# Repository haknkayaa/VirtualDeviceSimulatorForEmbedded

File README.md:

# Virtual Device Simulator for Embedded (VDS4E)

**Run Embedded Linux applications against virtual SPI, I²C, GPIO, UART and Ethernet devices without the physical target board.**

VDS4E is a hardwareless integration-testing environment for Embedded Linux software. It exposes virtual peripherals through normal Linux userspace interfaces such as `/dev/spidevX.Y`, `/dev/i2c-N`, `/dev/gpiochipN` and PTYs, allowing native x86_64 builds of production applications and standard Linux tools to exercise stateful device models on a development workstation.

VDS4E is not a CPU or board emulator. It focuses on the boundary between an Embedded Linux application and the device interfaces it already uses.

## See VDS4E

[Website](https://vds4e.dev) · [Watch the product film](https://vds4e.dev/#product-film) · [GitHub Releases](https://github.com/haknkayaa/VirtualDeviceSimulatorForEmbedded/releases)

VDS4E includes a browser-based engineering workbench for live device bring-up,
adapter configuration, register inspection, transaction tracing, logic analysis,
scenario execution and fault diagnosis. The UI runs with the packaged server;
no separate Web server is required for release installations.

## Why VDS4E?

Traditional mocks often replace application code paths. Full-system emulators model much more of the machine than many application-level tests need. VDS4E sits between those approaches:

- **No VDS-specific API in the application.** Production code continues to use the Linux device ABI.
- **Kernel-visible interfaces.** SPI, I²C and GPIO can be exercised through normal device nodes; UART uses a standard PTY.
- **Stateful peripherals.** Device packages can model registers, bitfields, memory, state machines, timed operations, faults and reset behavior.
- **Declarative models.** Peripheral behavior lives in versioned device packages rather than application-side test doubles.
- **Cross-device topology.** Public device signals can drive GPIO lines, enabling flows such as sensor DRDY → GPIO edge → bus read.
- **Observable execution.** Transactions, registers, state, faults, scenarios and telemetry are available through the control plane.
- **Automation friendly.** Headless scenarios can produce JSON and JUnit results for integration and CI workflows.

## Architecture

```text
┌──────────────────────────────────────────────────────────────────────┐
│ Embedded Linux application / standard Linux tool                    │
│ spidev_test · i2c-tools · libgpiod tools · normal application code  │
└───────────────────────────────┬──────────────────────────────────────┘
                                │ normal Linux userspace ABI
                                ▼
┌──────────────────────────────────────────────────────────────────────┐
│ VDS4E host adapters                                                  │
│ SPI CUSE · I²C CUSE · gpio-sim · UART PTY                           │
└───────────────────────────────┬──────────────────────────────────────┘
                                │ framed Protobuf / Unix socket
                                ▼
┌──────────────────────────────────────────────────────────────────────┐
│ VDS4E runtime                                                        │
│ device registry · registers · behavior · virtual time · topology     │
└───────────────────────────────┬──────────────────────────────────────┘
                                │
                                ▼
┌──────────────────────────────────────────────────────────────────────┐
│ Declarative device packages                                         │
│ model · flows · scenarios · fixtures · docs · assets                 │
└──────────────────────────────────────────────────────────────────────┘

Control & observability: REST API · WebSocket events · React Web UI
```

The detailed design and architectural boundaries are documented in [VDS4E_ARCHITECTURE.md](VDS4E_ARCHITECTURE.md).

## Supported interfaces

| Interface | Linux-facing endpoint | Runtime support | Typical clients |
| --- | --- | --- | --- |
| SPI / spidev | `/dev/spidevX.Y` via CUSE | `generic-spi-command` | production spidev applications, upstream `spidev_test` |
| I²C / i2c-dev | `/dev/i2c-N` via CUSE | `generic-i2c-register`, AT24C EEPROM | `i2cdetect`, `i2cget`, `i2cset`, `i2ctransfer`, libi2c applications |
| GPIO | real `/dev/gpiochipN` via kernel `gpio-sim` | `generic-gpio-bank` | `gpiodetect`, `gpioinfo`, `gpioget`, `gpioset`, `gpiomon`, libgpiod applications |
| UART / TTY | kernel-assigned `/dev/pts/N` | `generic-uart-responder` | applications using `open/read/write` and termios |
| QSPI multi-lane / DTR | native VDS4E transaction path | SPI wire-setting validation | VDS4E native clients |
| Ethernet / CAN / USB | — | not implemented | — |

SPI and I²C CUSE adapters and the GPIO `gpio-sim` integration require appropriate host-kernel support and privileges. UART PTY operation is unprivileged.

## What's available on `main`

| Capability | What you can do |
| --- | --- |
| **Bring-up-first Overview** | Follow the Linux device node → adapter → virtual peripheral path, inspect live traffic, runtime state, problem diagnostics, scenario progress and bus activity. |
| **Register and device workbench** | Inspect registers, bitfields, state, commands, fault controls, configuration and transaction history for each device. |
| **Transaction and logic analysis** | Examine bus requests/responses, protocol data, failures, virtual signals and capture timelines; filter failed transactions and deep-link to a capture. |
| **Declarative device modeling** | Build versioned SPI, I²C, GPIO and UART device packages with registers, command behavior, state transitions, time-dependent operations and fault injection. |
| **Board-level signal topology** | Route a modeled sensor's DRDY/IRQ output to a kernel-visible GPIO line; inspect connections, current signal levels and pending delayed deliveries in the UI or `GET /api/v1/topology`. |
| **Device Tree import** | Draft SPI/I²C/GPIO packages from a DTS file, plus a reviewed board summary and a GPIO-interrupt `topology.yaml` draft where supported. |
| **Scenario coverage** | See which declared commands, registers, states, transitions and faults a run actually exercised. Export machine-readable JSON and JUnit properties. |
| **Real Linux application examples** | Run sample C applications against SPI flash, I²C EEPROM, GPIO (libgpiod) and UART (PTY), using ordinary Linux interfaces rather than VDS4E-specific mocks. |

These are source-tree capabilities, not a promise that every feature above is
included in the latest published `.deb`. See [the changelog](CHANGELOG.md)
for changes made after the latest tagged release. DTS import produces editable
drafts, **not** validated device-specific behavior extracted automatically
from a hardware description.

## Quick start

### Install a release package

Tagged releases publish an `amd64` Debian package and SHA-256 checksum.
The latest published package is **v0.1.2**; newer capabilities described above
may require a build from the current `main` branch.

Download the package from [GitHub Releases](https://github.com/haknkayaa/VirtualDeviceSimulatorForEmbedded/releases), then install it:

```shell
sudo apt install ./vds4e_0.1.2_amd64.deb
```

Validate the installed configuration:

```shell
vds4e --check-config
```

Start VDS4E:

```shell
vds4e
```

Then open `http://127.0.0.1:8080/`. The same process serves the Web UI,
REST API, WebSocket event stream, and Unix-socket transaction data plane.

To run it as a system service instead:

```shell
sudo systemctl enable --now vds4e
```

The package installs the unit but does not enable or start it automatically.

The package installs:

- `vds4e`, `vds-server` and `vds-cli`
- SPI, I²C, GPIO and UART host adapters
- the built Web UI assets
- schemas and bundled example device models
- example Embedded Linux tools
- `/etc/vds4e/vds-server.yaml`

Package installation intentionally does not load privileged kernel modules automatically.

### Run from source

Building or running from source requires Rust (`rustup` / `cargo`), Node.js/npm, and system build tools. See [Getting started: Prerequisites](docs/guides/getting-started.md#prerequisites) for one-step installation instructions.

For development:

```shell
git clone https://github.com/haknkayaa/VirtualDeviceSimulatorForEmbedded.git
cd VirtualDeviceSimulatorForEmbedded
./run.sh
```

The development launcher starts the Web UI, control API and transaction data plane. See [Getting started](docs/guides/getting-started.md) for privilege details.

For the staged production-style build:

```shell
./configure
./build.sh
sudo ./install
```

## Device packages

A device is a self-contained, versionable package:

```text
my-device/
├── device-package.yaml
├── model/
│   └── device.yaml
├── flows/
│   └── behavior.yaml
├── scenarios/
├── fixtures/
├── docs/
└── assets/
```

Create and validate a package:

```shell
vds-cli device-package new ./my-sensor \
  --id my-sensor \
  --name "My Sensor" \
  --bus i2c

vds-cli device-package validate ./my-sensor
```

The bundled examples include generic SPI/I²C/GPIO/UART devices, an Ethernet ARP/ICMP host, AT24C EEPROM models and a Micron MT25QL256 flash model.

### Example applications

The repository includes standalone Embedded Linux examples that exercise the
same interfaces as ordinary production applications:

| Example | Linux interface | What it exercises |
| --- | --- | --- |
| [Micron MT25QL256](examples/micron-mt25ql256-embedded/) | SPI `/dev/spidevX.Y` | flash identification and command transactions |
| [Atmel AT24C256](examples/atmel-at24c256-embedded/) | I²C `/dev/i2c-N` | EEPROM address and data transactions |
| [Generic GPIO tool](examples/generic-gpio-embedded/) | libgpiod `/dev/gpiochipN` | line inspection, input/output and edge monitoring |
| [UART ping](examples/generic-uart-embedded/) | PTY `/dev/pts/N` | serial request/response |
| [Ethernet TAP](docs/guides/ethernet.md) | TAP `vdsN` | ARP resolution and IPv4 ICMP Echo from normal Linux tools |

From a source checkout with prerequisites installed:

```shell
./examples/run_all.sh --build-only
```

Start VDS4E and load the relevant adapters and device bindings before running
the examples. `./examples/run_all.sh` also attempts to exercise discovered
device nodes; it may need host privileges for the kernel-backed interfaces.
The actual `gpiochipN` and PTY numbers depend on the host.

See the [Device Package SDK](docs/development/device-package-sdk.md), [behavior-flow reference](docs/device-models/device-behavior-flow-reference.md), and package/model schemas under [schemas/](schemas/).

## Cross-device signals

Device models can expose public boolean output signals and connect them to device-driven GPIO lines through a board topology.

A typical flow is:

```text
sensor schedules conversion completion
        ↓
sensor.drdy becomes high
        ↓
VDS4E topology routes the signal
        ↓
virtual GPIO line changes
        ↓
/dev/gpiochipN reports an edge
        ↓
application reads the sensor over SPI/I²C
        ↓
read-clear status deasserts DRDY
```

This allows application behavior based on interrupts/data-ready lines to be exercised without adding simulator-specific code to the application.

The workbench and `GET /api/v1/topology` also expose a **read-only view** of
the attached connections, last sampled source levels and delayed deliveries.

See [Topology](docs/guides/topology.md).

## Scenarios and deterministic device behavior

Headless scenarios use a manual virtual clock. Device-model operations such as state transitions, delayed actions, faults and timed write/erase behavior can therefore be reproduced independently of host CPU speed.

Example:

```shell
vds-cli scenario run \
  device-models/examples/micron-mt25ql256aba8esf-0sit/scenarios/01-read-jedec-id.yaml \
  --config config/vds-server.yaml \
  --json-output /tmp/result.json \
  --junit-output /tmp/result.xml
```

The live server uses a real-time-backed simulator clock. Live runs therefore retain deterministic device-model semantics but are still subject to normal operating-system scheduling jitter. VDS4E does not claim whole-system or bit-for-bit determinism for live native processes.

## Scenario coverage

Scenario results can report model-level coverage, so a passing test does not
silently imply that every declared behavior was exercised. Coverage tracks:

- commands sent to a modeled device;
- registers reached through normal device operations;
- entered/exited states and observed state transitions;
- triggered fault definitions.

You can inspect coverage in the CLI output, scenario JSON results, JUnit
properties, the Visual Scenario Editor and the Overview's latest-run panel.
Coverage is **informational**; it does not automatically fail CI when a
threshold is missed.

Read the [coverage reference](docs/development/scenario-coverage.md)
and [ADR 0013](docs/adr/0013-measure-scenario-coverage-against-device-models.md)
for the exact counting rules and current SPI-scenario scope.

## Control and observability

The server provides:

- REST control API
- WebSocket event stream with bounded replay
- optional SQLite event persistence
- transaction and register inspection
- device state and fault control
- scenario execution
- adapter management
- React Web UI

High-frequency hardware transactions do **not** travel over REST. Native adapters use the framed Protobuf Unix-socket data plane.

Default development endpoints:

```text
Control API:  http://127.0.0.1:8080/api/v1
Web UI:       http://127.0.0.1:4174
Data plane:   /tmp/vds4e.sock
```

## Hardware-description import

The `vds-importer` crate can draft declarative models from:

- CMSIS-SVD register descriptions
- Device Tree source

Importer output is intentionally a starting point rather than a finished behavioral model. Device-specific semantics still need to be reviewed and completed by the model author.

Draft device packages for enabled SPI, I²C and GPIO peripherals in a board's Device Tree (available on `main`):

```shell
vds-cli import dts board.dts --output drafts/
```

When a peripheral's `interrupt-parent` is a GPIO controller of the board, the
import also drafts that controller as a GPIO bank and writes
`drafts/topology.yaml`, connecting the peripheral's new `irq` output (driven by
bit 0 of a placeholder `IRQ_STATE` register) to the line its `interrupts`
names. Every draft, and the topology, is loaded the way the server loads them
before the command succeeds. `drafts/board.md` lists each package with its bus controller,
endpoint (SPI chip select or I2C address), compatible strings and interrupts,
the nodes that were skipped (disabled, or a bus without a VDS4E runtime), and
the `device_packages` entries to add to `vds-server.yaml`. Pass
`--include-disabled` to draft `status = "disabled"` nodes too.

## What VDS4E does not simulate

VDS4E provides functional peripheral simulation. It does not currently model:

- CPU instruction execution
- a complete SoC or board boot
- electrical characteristics or signal integrity
- controller DMA/IRQ timing
- analog behavior
- Ethernet, CAN or USB runtime devices
- full-system checkpoint/restore or record/replay

Use QEMU, Renode or another full-system platform when CPU/SoC emulation is the requirement. Use hardware-in-the-loop and real-target testing for electrical, timing and hardware-integration validation.

For recorded, unprivileged device replay, [umockdev](https://github.com/martinpitt/umockdev) may be a lighter fit. VDS4E is aimed at cases where stateful modeled behavior, kernel-visible interfaces, shared device state and cross-device interaction matter.

## Verification

The regular CI validates the Rust workspace, Web UI, native adapters and example applications.

Equivalent local checks include:

```shell
cargo fmt --all -- --check
cargo clippy --workspace --all-targets --locked -- -D warnings
cargo test --workspace --locked

npm --prefix apps/vds-web ci
npm --prefix apps/vds-web run lint
npm --prefix apps/vds-web run typecheck
npm --prefix apps/vds-web run test:run
npm --prefix apps/vds-web run build
```

A real Linux ABI E2E harness is available under `tests/e2e/` for privileged integration testing with standard Linux tools and kernel-backed interfaces.

## Documentation

| Document | Purpose |
| --- | --- |
| [Documentation index](docs/README.md) | map of user, contributor and architecture documentation |
| [Getting started](docs/guides/getting-started.md) | prerequisites, development workspace, staged build and installation |
| [First virtual device](docs/tutorials/first-virtual-device.md) | create an I²C model and exercise it through a real `/dev/i2c-N` endpoint |
| [Control-plane API](docs/guides/api.md) | REST resources, error contract and replayable WebSocket events |
| [Architecture](VDS4E_ARCHITECTURE.md) | authoritative system architecture and boundaries |
| [Testing](docs/guides/testing.md) | local checks, native adapters, real Linux ABI E2E and CI scope |
| [Releases](docs/guides/releases.md) | version/tag rules and Debian release workflow |
| [Troubleshooting](docs/guides/troubleshooting.md) | common CUSE, gpio-sim, permissions, PTY and configuration issues |
| [SPI / I²C / GPIO / UART](docs/guides/) | Linux host-interface guides and examples |
| [Ethernet TAP](docs/guides/ethernet.md) | Linux TAP adapter, ARP/ICMP host model and configuration |
| [Topology guide](docs/guides/topology.md) | cross-device signal routing |
| [Device Package SDK](docs/development/device-package-sdk.md) | package contract and author workflow |
| [Scenario coverage](docs/development/scenario-coverage.md) | coverage accounting for commands, registers, states, transitions and faults |
| [C example applications](examples/) | hardware-facing sample tools and run-all script |
| [ADRs](docs/adr/README.md) | architecture decisions |
| [Roadmap](docs/ROADMAP.md) | planned capabilities |
| [Contributing](CONTRIBUTING.md) | development and contribution guidance |
| [Security](SECURITY.md) | security policy |

## Project boundaries

The project intentionally keeps these responsibilities separate:

- the server owns authoritative virtual-device state;
- host adapters translate Linux ABIs and do not contain device semantics;
- the Web UI is a control and observability client, not a device runtime;
- high-frequency transactions use the native Unix-socket data plane;
- behavior comes from declarative device packages;
- privileged kernel integration is isolated from the core runtime.

These boundaries are part of the product design, not just implementation details.

## License

Licensed under the [Apache License 2.0](LICENSE).

## Maintainer

Hakan Kaya ([@haknkayaa](https://github.com/haknkayaa))

VDS4E is currently developed independently by Hakan Kaya. The open-source core is available under Apache 2.0.

Contact: [hakan@vds4e.dev](mailto:hakan@vds4e.dev) · [Project website](https://vds4e.dev)

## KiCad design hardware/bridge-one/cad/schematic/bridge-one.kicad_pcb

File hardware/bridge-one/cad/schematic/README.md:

# Bridge One schematic (generated)

`design.py` is the single source of truth: functional groups, parts, pin-to-net
maps and the notes printed in each group box. Do not edit the `.kicad_sch`
files by hand; regenerate them.

```bash
python3 symbols/make_symbols.py      # project symbols (RSV translators, TPS2553)
python3 ../footprints/make_footprints.py   # TI DQA / YXC land patterns
python3 render.py                    # root + one hierarchical sheet per group
python3 board.py                     # bridge-one.kicad_pcb: all parts, pad nets, linked to symbols
kicad-cli sch erc bridge-one.kicad_sch
kicad-cli sch export netlist --format kicadsexpr -o /tmp/bridge-one.net bridge-one.kicad_sch
python3 tools/verify_netlist.py /tmp/bridge-one.net   # must report 0 mismatches
kicad-cli sch export pdf -o bridge-one-schematic.pdf bridge-one.kicad_sch
```

Nets used in more than one group become global labels; group-internal nets are
local labels. Every symbol pin must be assigned a net or listed as no-connect,
or `render.py` refuses to write the schematic.

`board.py` places every design.py part (anchors from ../preview/generate_preview.py
plus NEW_ANCHORS; passives auto-placed next to the part they connect to), assigns
pad nets, links footprints to schematic symbols (deterministic UUIDs), restores
the JLCPCB 4-layer rules in bridge-one.kicad_pro, and writes the STEP and
placement.json used by ../enclosure/generate_enclosure.py.

Status (sch0.4, 2026-10-14): TPS3808G01 FPGA rail supervisor and VTREF overvoltage
disconnect added (research/vtref-ovp-and-fpga-supervisor.md); PCA9306 replaced by
PCA9617ADP (research/i2c-translator-replacement.md); review fixes applied (research/review-codex-sch0.1.md,
research/review-kicad-happy-sch0.1.md, research/footprint-verification.md).
ERC: only intentional warnings (unused translator inputs tied to GND, TPS22917 QOD
tied to VOUT). Netlist matches design.py exactly. PCB: 215 footprints, unrouted;
DRC errors are only unrouted nets, H2/H4 inside the module's conservative antenna
keepout (symmetric holes by request) and a GCT USB-C library footprint hole note.

Open: power budget vs F1 hold with aux outputs enabled, ESP32 open-drain low <= 0.4 V
for the PCA9617A B side (bench), OLED FPC pin-1 mapping check on samples, 32 MB PSRAM
option, KLS USB-C footprint swap, routing and bottom silkscreen cleanup.

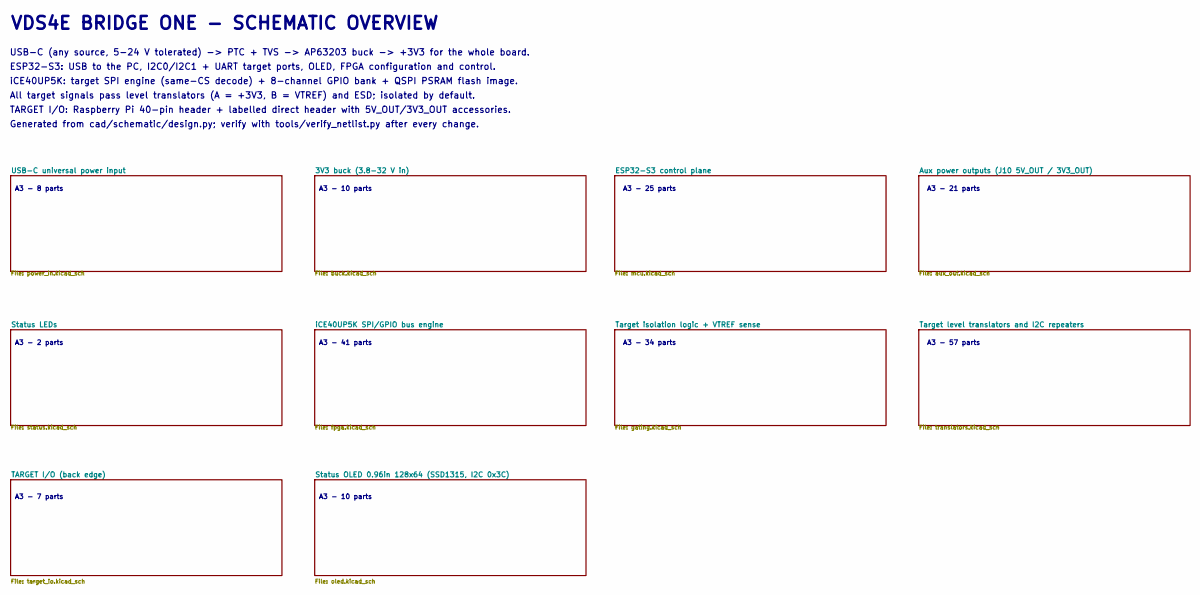
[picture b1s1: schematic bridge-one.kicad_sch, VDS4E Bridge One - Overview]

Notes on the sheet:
USB-C (any source, 5-24 V tolerated) -> PTC + TVS -> AP63203 buck -> +3V3 for the whole board.
iCE40UP5K: target SPI engine (same-CS decode) + 8-channel GPIO bank + QSPI PSRAM flash image.
VDS4E BRIDGE ONE - SCHEMATIC OVERVIEW
A3 - 10 parts
A3 - 8 parts
A3 - 7 parts
TARGET I/O: Raspberry Pi 40-pin header + labelled direct header with 5V_OUT/3V3_OUT accessories.
A3 - 21 parts
All target signals pass level translators (A = +3V3, B = VTREF) and ESD; isolated by default.
A3 - 2 parts
A3 - 25 parts
Generated from cad/schematic/design.py; verify with tools/verify_netlist.py after every change.
A3 - 41 parts
A3 - 57 parts
A3 - 34 parts
ESP32-S3: USB to the PC, I2C0/I2C1 + UART target ports, OLED, FPGA configuration and control.

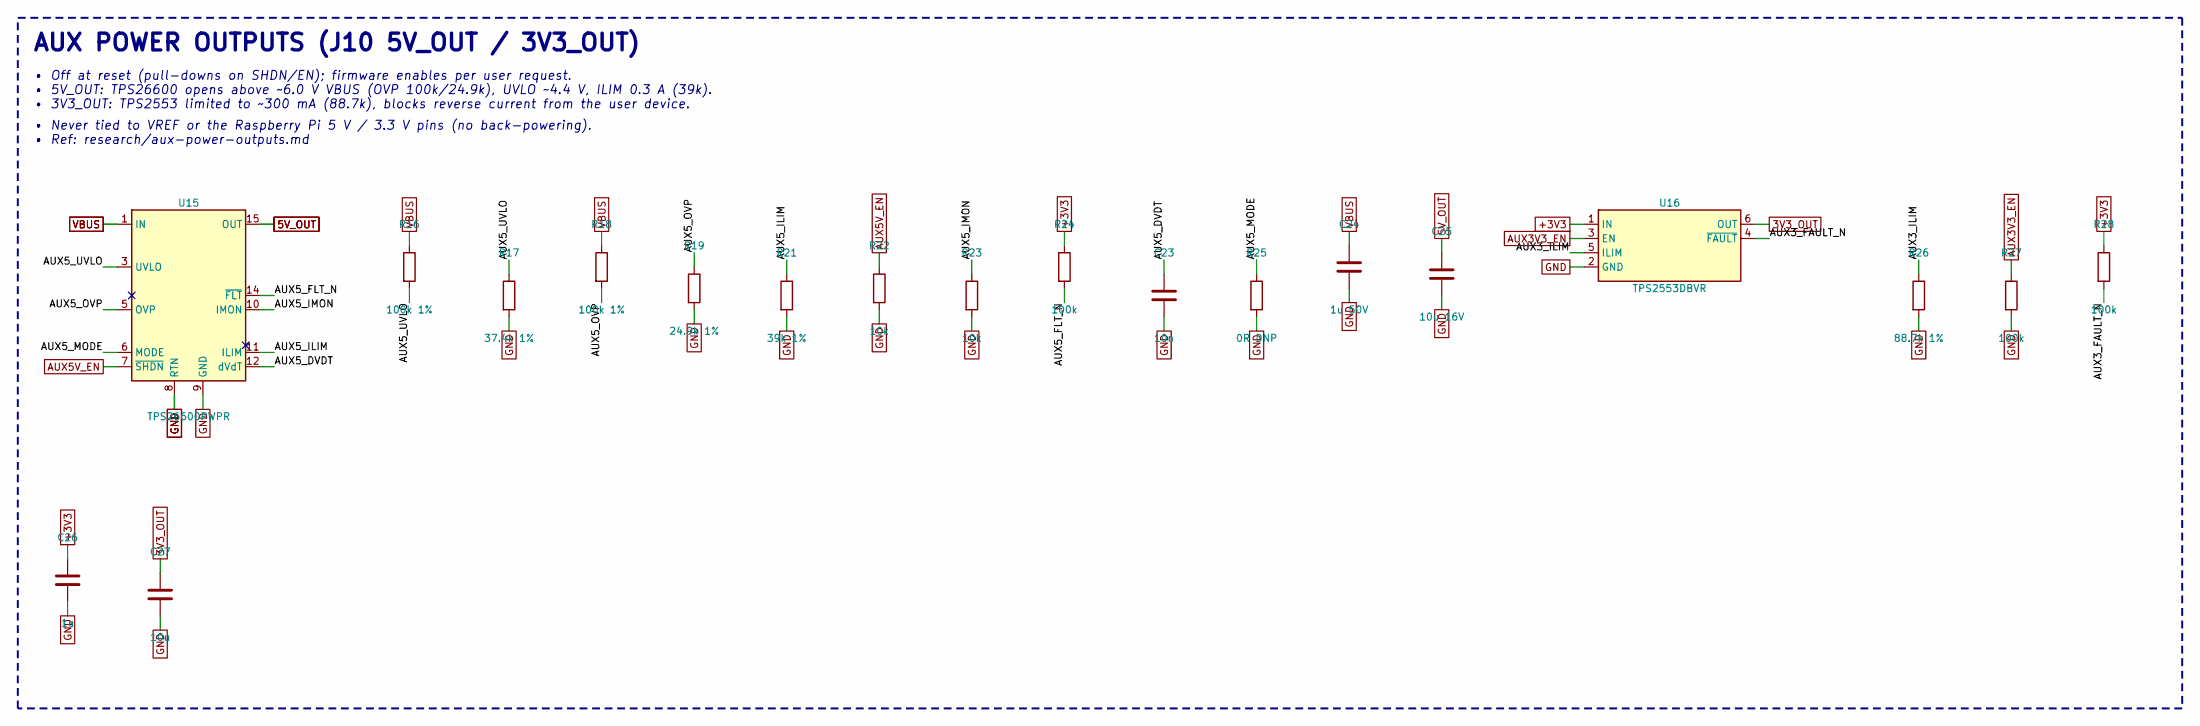
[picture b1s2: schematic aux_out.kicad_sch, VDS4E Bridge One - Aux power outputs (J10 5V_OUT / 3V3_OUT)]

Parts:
C23: 10n; C_0402_1005Metric
C24: 1u 50V; C_0603_1608Metric
C25: 10u 16V; C_0805_2012Metric
C26: 1u; C_0402_1005Metric
C27: 10u; C_0805_2012Metric
R16, R18: 100k 1%; R_0402_1005Metric
R17: 37.4k 1%; R_0402_1005Metric
R19: 24.9k 1%; R_0402_1005Metric
R21: 39k 1%; R_0402_1005Metric
R22, R23: 10k; R_0402_1005Metric
R24, R27, R28: 100k; R_0402_1005Metric
R25: 0R DNP; R_0402_1005Metric
R26: 88.7k 1%; R_0402_1005Metric
U15: TPS26600PWPR; HTSSOP-16-1EP_4.4x5mm_P0.65mm_EP3.4x5mm; MPN TPS26600PWPR
U16: TPS2553DBVR; SOT-23-6; MPN TPS2553DBVR

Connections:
3V3_OUT: C27.1, U16.6 (OUT); also elsewhere on the board
5V_OUT: C25.1, U15.15 (OUT), U15.16 (OUT); also elsewhere on the board
AUX3V3_EN: R27.1, U16.3 (EN); also elsewhere on the board
AUX3_FAULT_N: R28.2, U16.4 (~FAULT)
AUX3_ILIM: R26.1, U16.5 (ILIM)
AUX5V_EN: R22.1, U15.7 (~SHDN); also elsewhere on the board
AUX5_DVDT: C23.1, U15.12 (dVdT)
AUX5_FLT_N: R24.2, U15.14 (~FLT)
AUX5_ILIM: R21.1, U15.11 (ILIM)
AUX5_IMON: R23.1, U15.10 (IMON)
AUX5_MODE: R25.1, U15.6 (MODE)
AUX5_OVP: R18.2, R19.1, U15.5 (OVP); also elsewhere on the board
AUX5_UVLO: R16.2, R17.1, U15.3 (UVLO); also elsewhere on the board
VBUS: C24.1, R16.1, R18.1, U15.1 (IN), U15.2 (IN); also elsewhere on the board

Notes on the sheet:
• Never tied to VREF or the Raspberry Pi 5 V / 3.3 V pins (no back-powering).
• 5V_OUT: TPS26600 opens above ~6.0 V VBUS (OVP 100k/24.9k), UVLO ~4.4 V, ILIM 0.3 A (39k).
• 3V3_OUT: TPS2553 limited to ~300 mA (88.7k), blocks reverse current from the user device.
AUX POWER OUTPUTS (J10 5V_OUT / 3V3_OUT)
• Ref: research/aux-power-outputs.md
• Off at reset (pull-downs on SHDN/EN); firmware enables per user request.

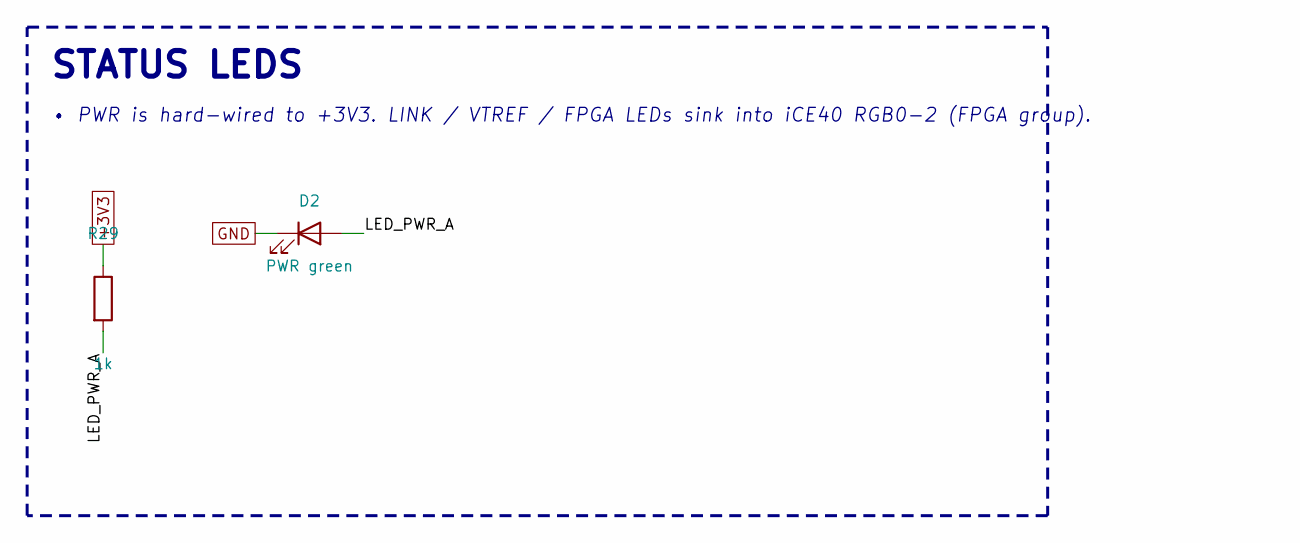
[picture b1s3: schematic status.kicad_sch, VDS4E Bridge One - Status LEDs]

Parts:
D2: PWR green; LED_0603_1608Metric
R29: 1k; R_0402_1005Metric

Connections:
LED_PWR_A: D2.2 (A), R29.2

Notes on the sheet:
• PWR is hard-wired to +3V3. LINK / VTREF / FPGA LEDs sink into iCE40 RGB0-2 (FPGA group).
STATUS LEDS

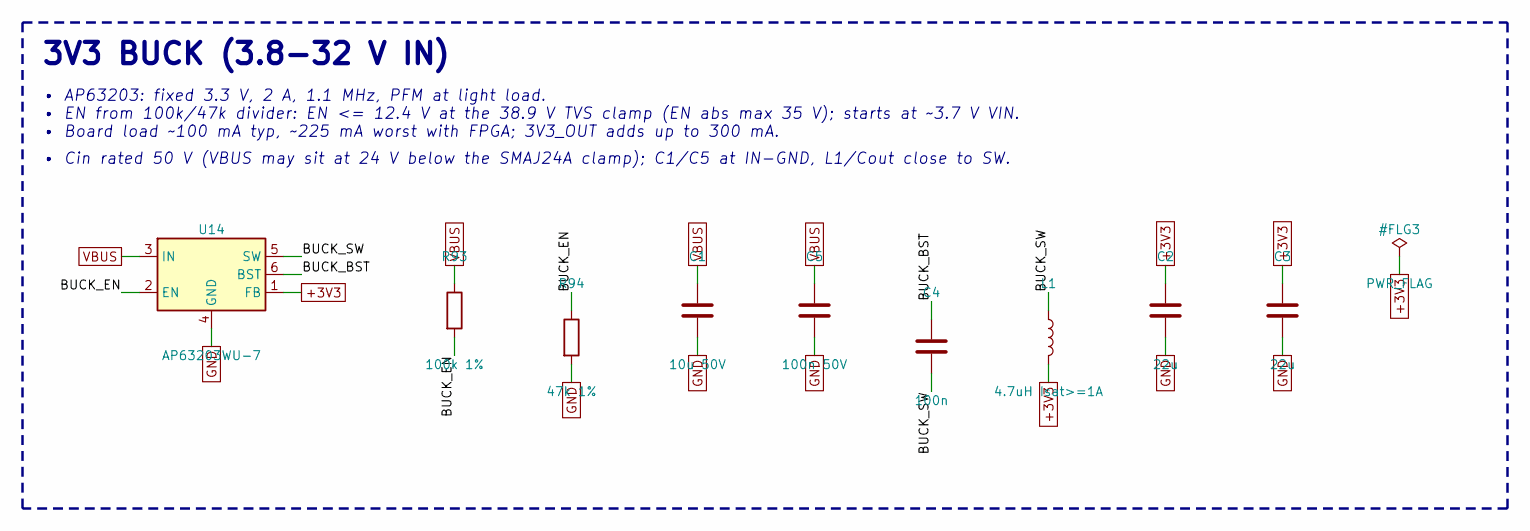
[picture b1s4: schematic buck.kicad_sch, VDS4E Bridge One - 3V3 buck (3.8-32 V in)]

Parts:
C1: 10u 50V; C_1206_3216Metric
C2, C3: 22u; C_0805_2012Metric
C4: 100n; C_0603_1608Metric
C5: 100n 50V; C_0603_1608Metric
L1: 4.7uH Isat>=1A; L_Taiyo-Yuden_NR-30xx; MPN NR3015N4R7A
R93: 100k 1%; R_0402_1005Metric
R94: 47k 1%; R_0402_1005Metric
U14: AP63203WU-7; TSOT-23-6; MPN AP63203WU-7

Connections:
BUCK_BST: C4.1, U14.6 (BST)
BUCK_EN: R93.2, R94.1, U14.2 (EN)
BUCK_SW: C4.2, L1.1, U14.5 (SW)
VBUS: C1.1, C5.1, R93.1, U14.3 (IN); also elsewhere on the board

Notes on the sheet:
• AP63203: fixed 3.3 V, 2 A, 1.1 MHz, PFM at light load.
• Cin rated 50 V (VBUS may sit at 24 V below the SMAJ24A clamp); C1/C5 at IN-GND, L1/Cout close to SW.
3V3 BUCK (3.8-32 V IN)
• EN from 100k/47k divider: EN <= 12.4 V at the 38.9 V TVS clamp (EN abs max 35 V); starts at ~3.7 V VIN.
• Board load ~100 mA typ, ~225 mA worst with FPGA; 3V3_OUT adds up to 300 mA.

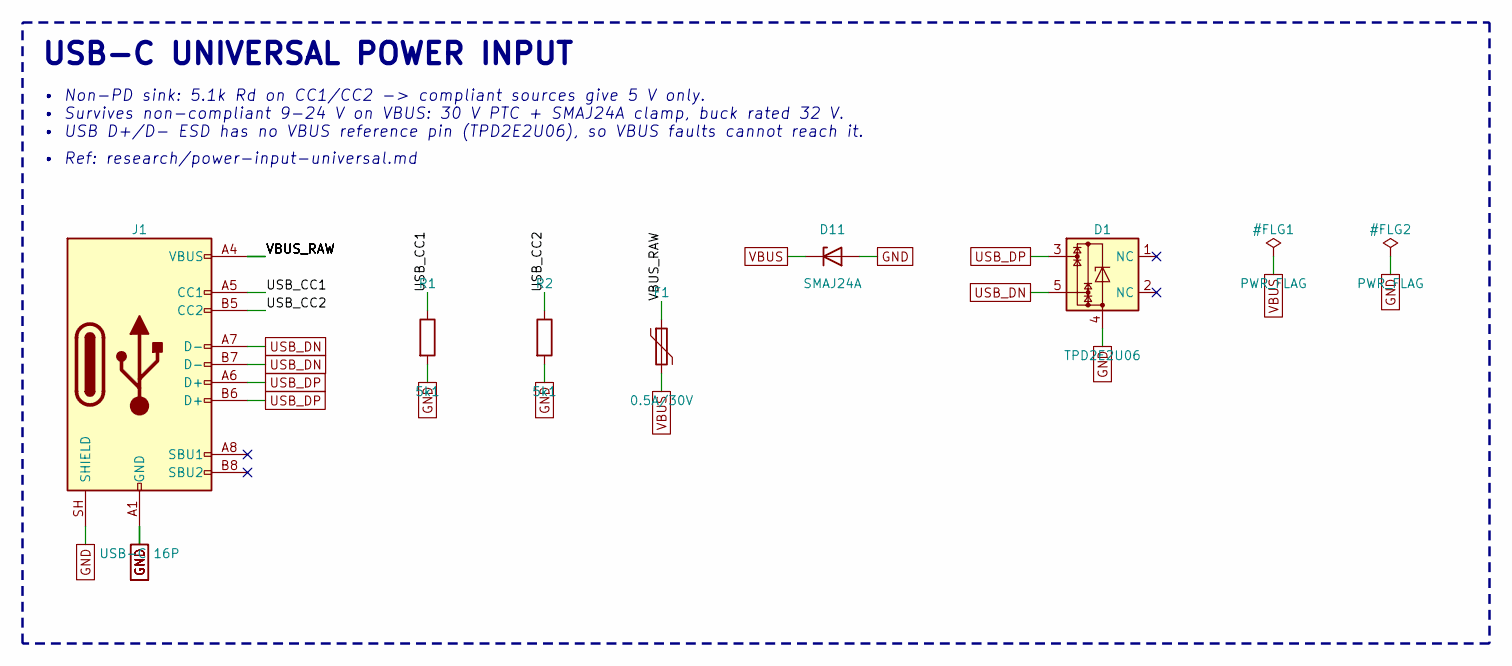
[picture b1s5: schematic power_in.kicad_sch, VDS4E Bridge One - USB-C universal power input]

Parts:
D1: TPD2E2U06; SOT-553; MPN TPD2E2U06DRLR
D11: SMAJ24A; D_SMA; MPN SMAJ24A
F1: 0.5A/30V; Fuse_1812_4532Metric; MPN BSMD1812-050-30V
J1: USB-C 16P; USB_C_Receptacle_GCT_USB4105-xx-A_16P_TopMnt_Horizontal; MPN USB4105-GF-A-120
R1, R2: 5k1; R_0402_1005Metric

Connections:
USB_CC1: J1.A5 (CC1), R1.1
USB_CC2: J1.B5 (CC2), R2.1
USB_DN: D1.5, J1.A7 (D-), J1.B7 (D-); also elsewhere on the board
USB_DP: D1.3, J1.A6 (D+), J1.B6 (D+); also elsewhere on the board
VBUS: D11.1 (K), F1.2; also elsewhere on the board
VBUS_RAW: F1.1, J1.A4 (VBUS), J1.A9 (VBUS), J1.B4 (VBUS), J1.B9 (VBUS)

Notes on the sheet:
• Ref: research/power-input-universal.md
• USB D+/D- ESD has no VBUS reference pin (TPD2E2U06), so VBUS faults cannot reach it.
• Survives non-compliant 9-24 V on VBUS: 30 V PTC + SMAJ24A clamp, buck rated 32 V.
• Non-PD sink: 5.1k Rd on CC1/CC2 -> compliant sources give 5 V only.
USB-C UNIVERSAL POWER INPUT

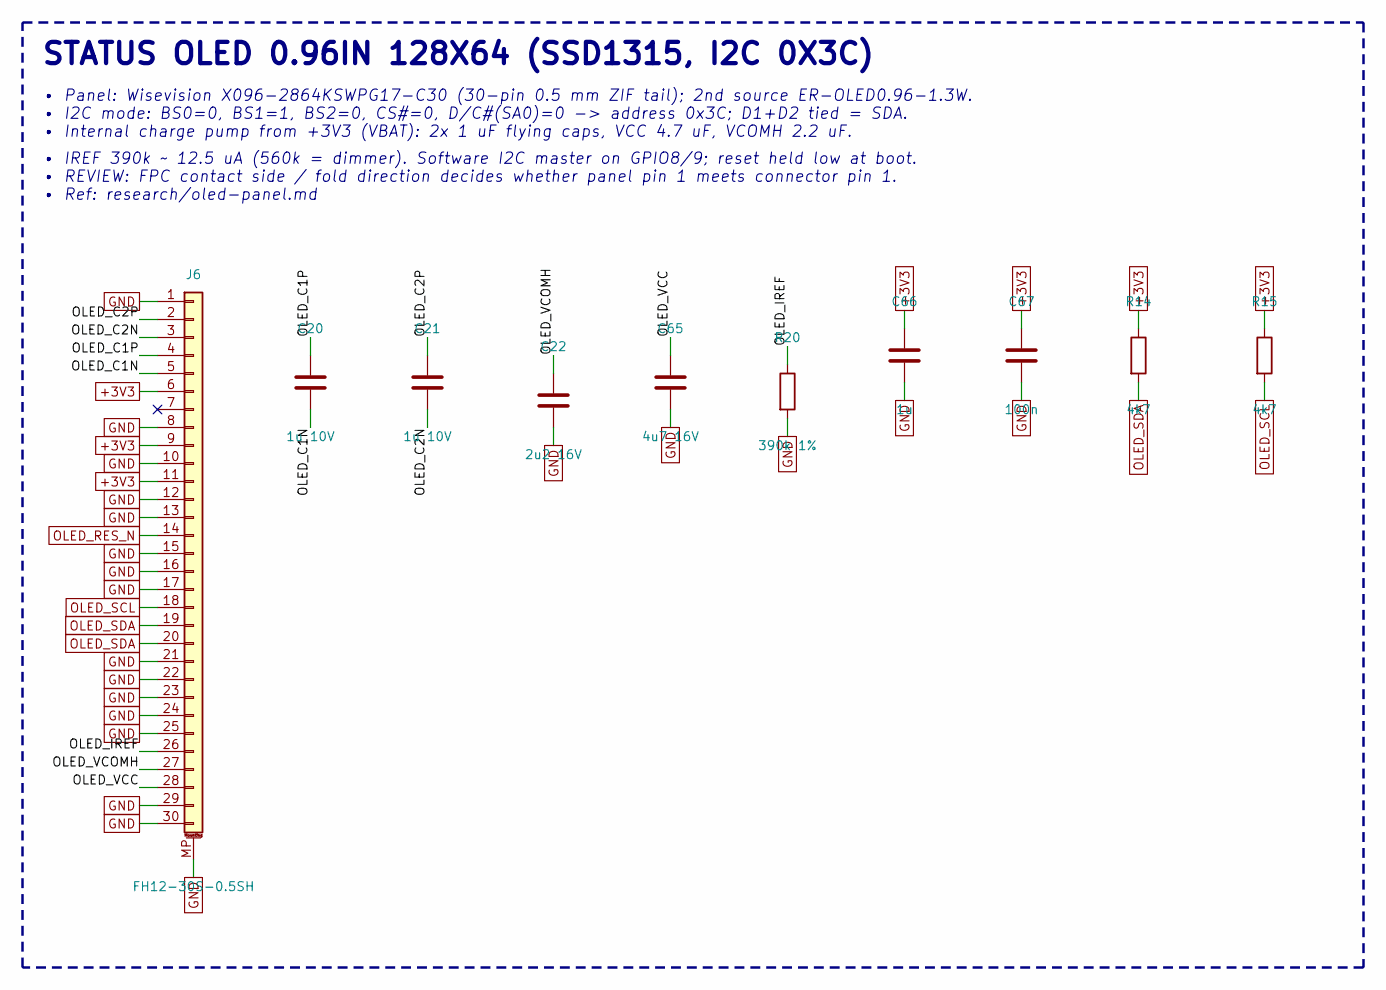
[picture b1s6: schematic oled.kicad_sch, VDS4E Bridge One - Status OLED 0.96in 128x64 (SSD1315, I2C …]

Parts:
C20, C21: 1u 10V; C_0402_1005Metric
C22: 2u2 16V; C_0402_1005Metric
C65: 4u7 16V; C_0603_1608Metric
C66: 1u; C_0402_1005Metric
C67: 100n; C_0402_1005Metric
J6: FH12-30S-0.5SH; Hirose_FH12-30S-0.5SH_1x30-1MP_P0.50mm_Horizontal; MPN FH12-30S-0.5SH(55)
R14, R15: 4k7; R_0402_1005Metric
R20: 390k 1%; R_0402_1005Metric

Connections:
OLED_C1N: C20.2, J6.5
OLED_C1P: C20.1, J6.4
OLED_C2N: C21.2, J6.3
OLED_C2P: C21.1, J6.2
OLED_IREF: J6.26, R20.1
OLED_RES_N: J6.14; also elsewhere on the board
OLED_SCL: J6.18, R15.2; also elsewhere on the board
OLED_SDA: J6.19, J6.20, R14.2; also elsewhere on the board
OLED_VCC: C65.1, J6.28
OLED_VCOMH: C22.1, J6.27

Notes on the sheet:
• I2C mode: BS0=0, BS1=1, BS2=0, CS#=0, D/C#(SA0)=0 -> address 0x3C; D1+D2 tied = SDA.
• Panel: Wisevision X096-2864KSWPG17-C30 (30-pin 0.5 mm ZIF tail); 2nd source ER-OLED0.96-1.3W.
• Ref: research/oled-panel.md
• IREF 390k ~ 12.5 uA (560k = dimmer). Software I2C master on GPIO8/9; reset held low at boot.
• Internal charge pump from +3V3 (VBAT): 2x 1 uF flying caps, VCC 4.7 uF, VCOMH 2.2 uF.
STATUS OLED 0.96IN 128X64 (SSD1315, I2C 0X3C)
• REVIEW: FPC contact side / fold direction decides whether panel pin 1 meets connector pin 1.

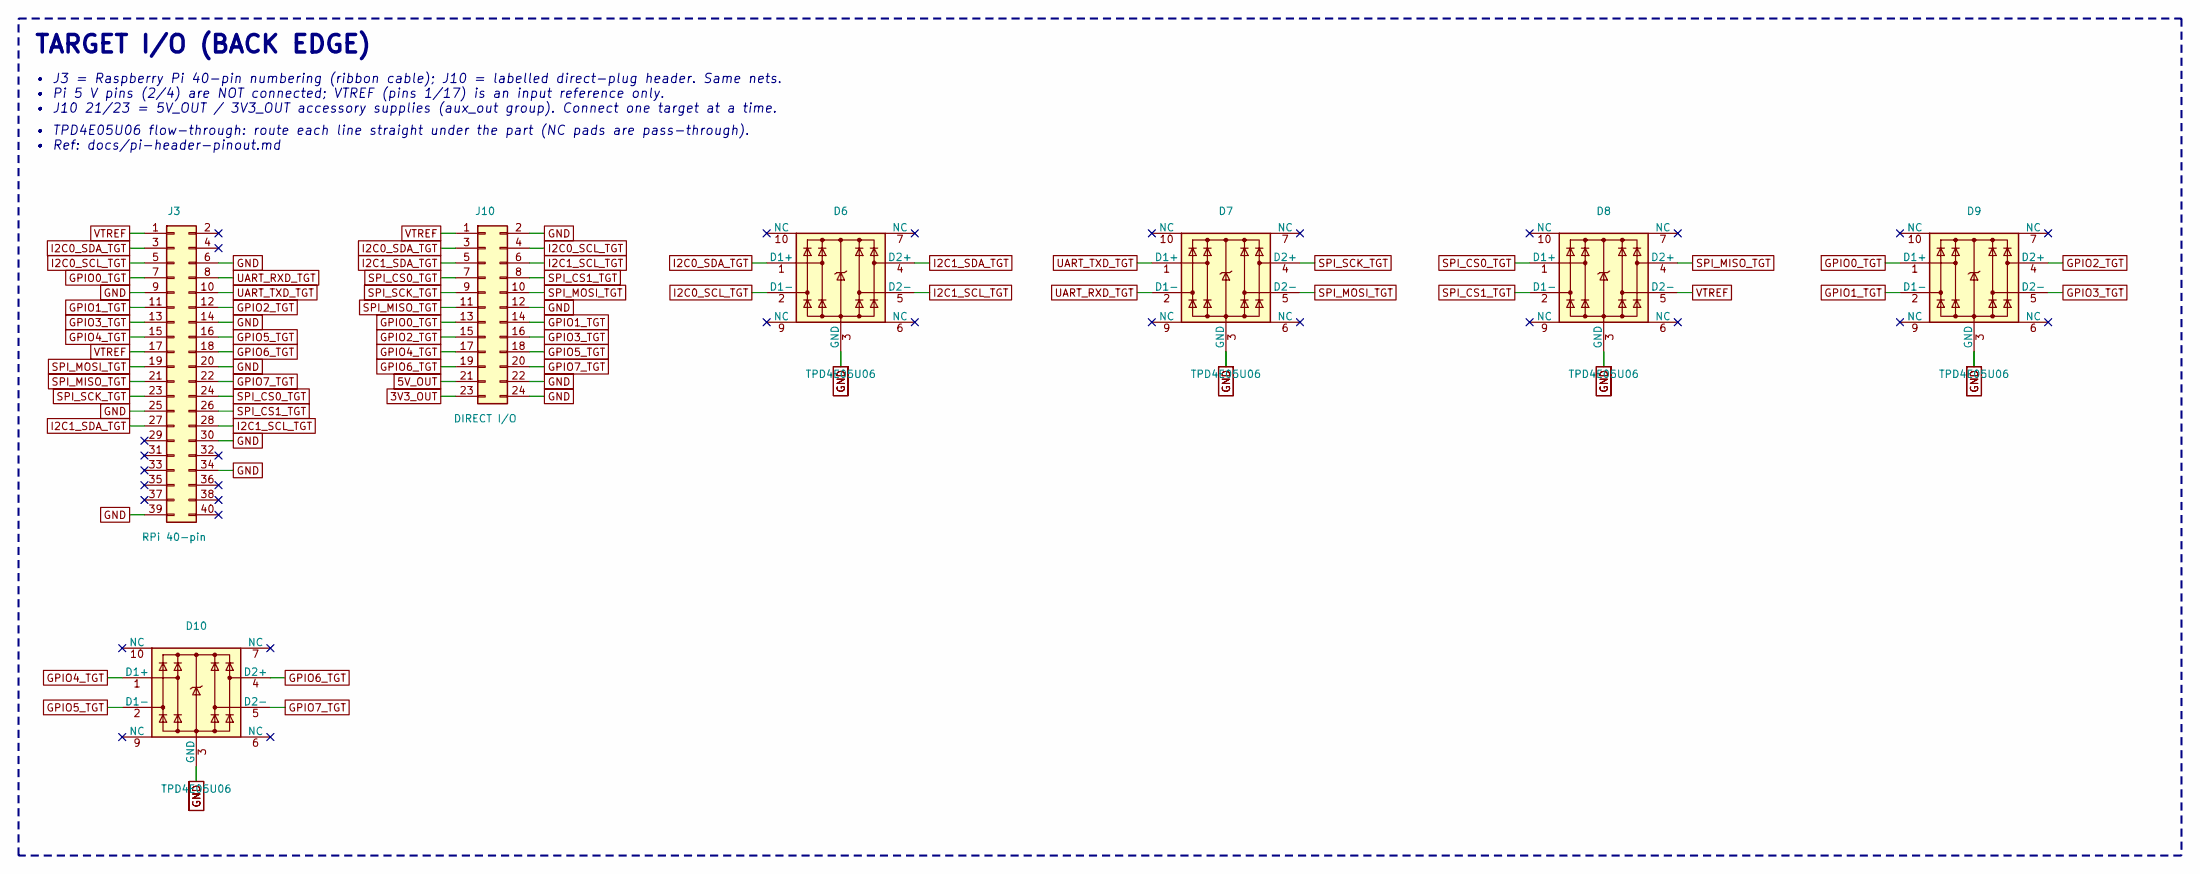
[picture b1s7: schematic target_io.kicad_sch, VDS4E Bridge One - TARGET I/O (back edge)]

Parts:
D6, D7, D8, D9, D10: TPD4E05U06; USON-10_2.5x1.0mm_P0.5mm_TI_DQA; MPN TPD4E05U06DQAR
J3: RPi 40-pin; PinHeader_2x20_P2.54mm_Vertical
J10: DIRECT I/O; PinHeader_2x12_P2.54mm_Vertical

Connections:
3V3_OUT: J10.23; also elsewhere on the board
5V_OUT: J10.21; also elsewhere on the board
GPIO0_TGT: D9.1 (D1+), J3.7, J10.13; also elsewhere on the board
GPIO1_TGT: D9.2 (D1-), J3.11, J10.14; also elsewhere on the board
GPIO2_TGT: D9.4 (D2+), J3.12, J10.15; also elsewhere on the board
GPIO3_TGT: D9.5 (D2-), J3.13, J10.16; also elsewhere on the board
GPIO4_TGT: D10.1 (D1+), J3.15, J10.17; also elsewhere on the board
GPIO5_TGT: D10.2 (D1-), J3.16, J10.18; also elsewhere on the board
GPIO6_TGT: D10.4 (D2+), J3.18, J10.19; also elsewhere on the board
GPIO7_TGT: D10.5 (D2-), J3.22, J10.20; also elsewhere on the board
SPI_CS0_TGT: D8.1 (D1+), J3.24, J10.7; also elsewhere on the board
SPI_CS1_TGT: D8.2 (D1-), J3.26, J10.8; also elsewhere on the board
SPI_MISO_TGT: D8.4 (D2+), J3.21, J10.11; also elsewhere on the board
SPI_MOSI_TGT: D7.5 (D2-), J3.19, J10.10; also elsewhere on the board
SPI_SCK_TGT: D7.4 (D2+), J3.23, J10.9; also elsewhere on the board
UART_RXD_TGT: D7.2 (D1-), J3.8; also elsewhere on the board
UART_TXD_TGT: D7.1 (D1+), J3.10; also elsewhere on the board
VTREF: D8.5 (D2-), J3.1, J3.17, J10.1; also elsewhere on the board

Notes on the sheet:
• TPD4E05U06 flow-through: route each line straight under the part (NC pads are pass-through).
• Pi 5 V pins (2/4) are NOT connected; VTREF (pins 1/17) is an input reference only.
TARGET I/O (BACK EDGE)
• J10 21/23 = 5V_OUT / 3V3_OUT accessory supplies (aux_out group). Connect one target at a time.
• J3 = Raspberry Pi 40-pin numbering (ribbon cable); J10 = labelled direct-plug header. Same nets.
• Ref: docs/pi-header-pinout.md

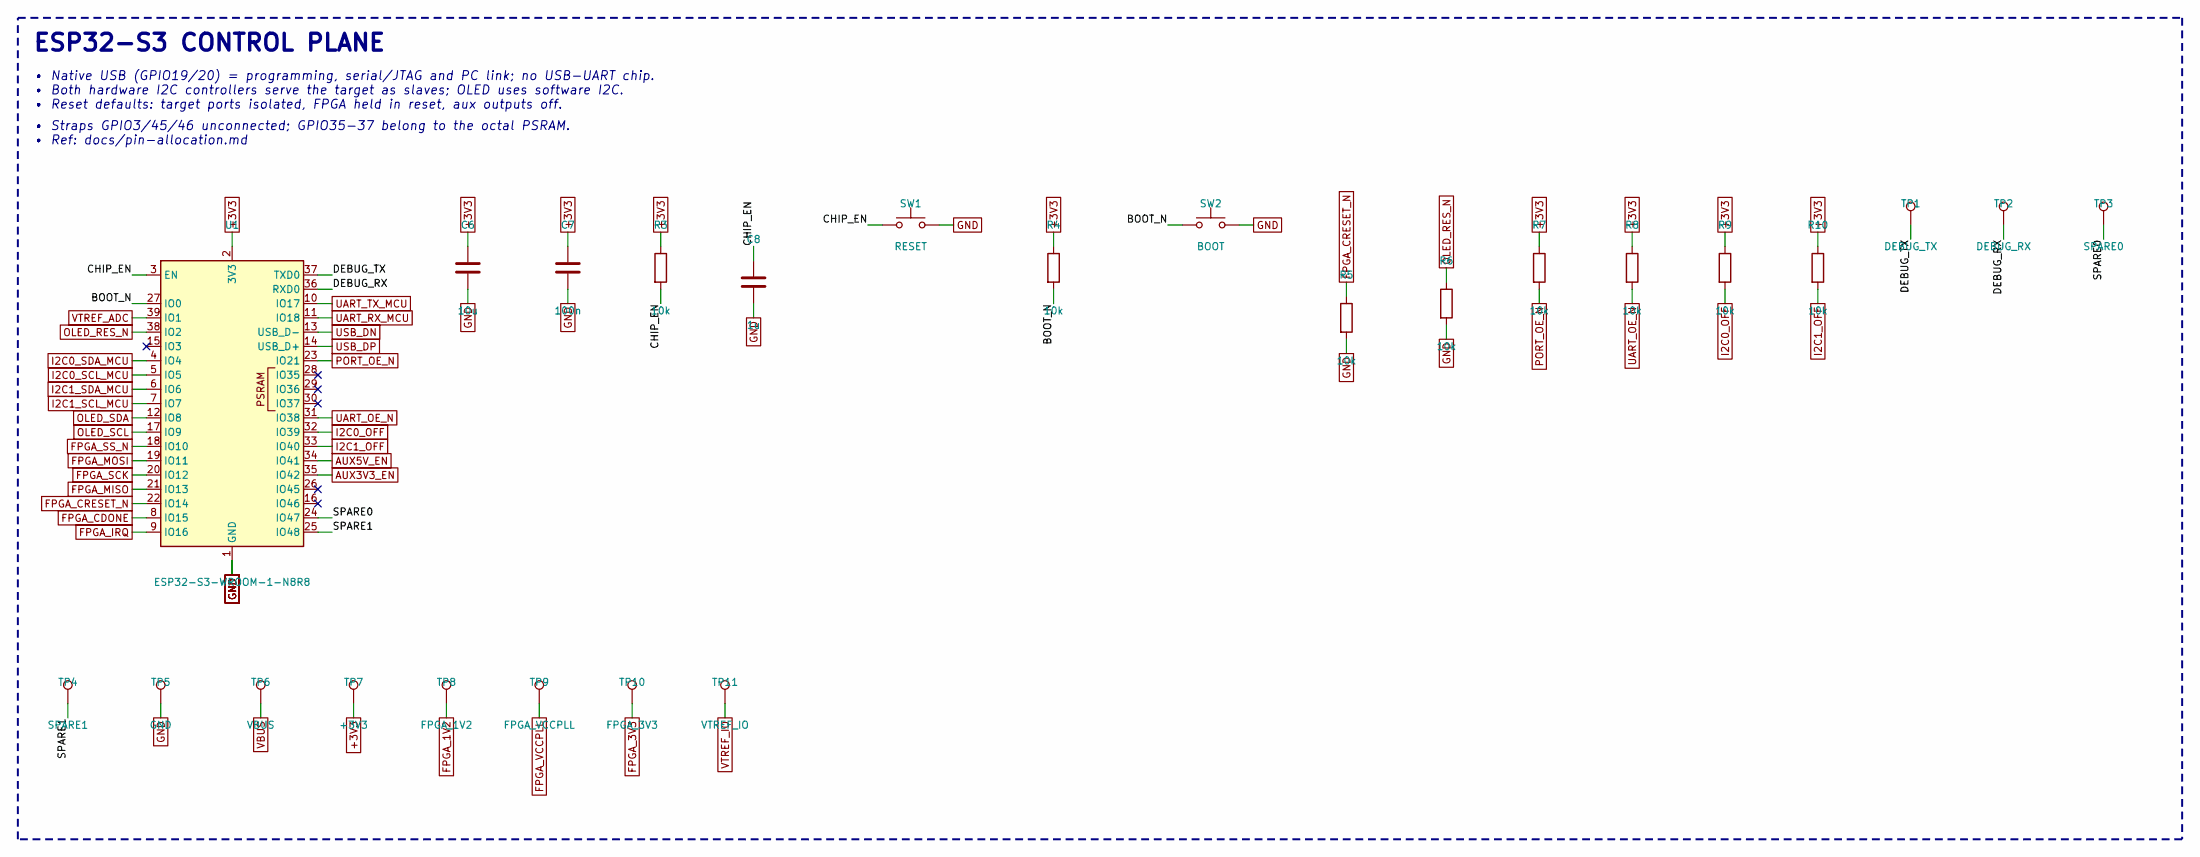
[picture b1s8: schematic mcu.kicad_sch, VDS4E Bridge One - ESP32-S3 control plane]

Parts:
C6: 10u; C_0805_2012Metric
C7: 100n; C_0402_1005Metric
C8: 1u; C_0402_1005Metric
R3, R4, R5, R6, R7, R8, R9, R10: 10k; R_0402_1005Metric
SW1: RESET; SW_SPST_EVQP7A; MPN EVQ-P7A01P
SW2: BOOT; SW_SPST_EVQP7A; MPN EVQ-P7A01P
TP1: DEBUG_TX; TestPoint_Pad_D1.0mm
TP2: DEBUG_RX; TestPoint_Pad_D1.0mm
TP3: SPARE0; TestPoint_Pad_D1.0mm
TP4: SPARE1; TestPoint_Pad_D1.0mm
TP5: GND; TestPoint_Pad_D1.0mm
TP6: VBUS; TestPoint_Pad_D1.0mm
TP7: +3V3; TestPoint_Pad_D1.0mm
TP8: FPGA_1V2; TestPoint_Pad_D1.0mm
TP9: FPGA_VCCPLL; TestPoint_Pad_D1.0mm
TP10: FPGA_3V3; TestPoint_Pad_D1.0mm
TP11: VTREF_IO; TestPoint_Pad_D1.0mm
U1: ESP32-S3-WROOM-1-N8R8; ESP32-S3-WROOM-1; MPN ESP32-S3-WROOM-1-N8R8

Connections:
AUX3V3_EN: U1.35 (IO42); also elsewhere on the board
AUX5V_EN: U1.34 (IO41); also elsewhere on the board
BOOT_N: R4.2, SW2.1, U1.27 (IO0)
CHIP_EN: C8.1, R3.2, SW1.1, U1.3 (EN)
DEBUG_RX: TP2.1, U1.36 (RXD0)
DEBUG_TX: TP1.1, U1.37 (TXD0)
FPGA_1V2: TP8.1; also elsewhere on the board
FPGA_3V3: TP10.1; also elsewhere on the board
FPGA_CDONE: U1.8 (IO15); also elsewhere on the board
FPGA_CRESET_N: R5.1, U1.22 (IO14); also elsewhere on the board
FPGA_IRQ: U1.9 (IO16); also elsewhere on the board
FPGA_MISO: U1.21 (IO13); also elsewhere on the board
FPGA_MOSI: U1.19 (IO11); also elsewhere on the board
FPGA_SCK: U1.20 (IO12); also elsewhere on the board
FPGA_SS_N: U1.18 (IO10); also elsewhere on the board
FPGA_VCCPLL: TP9.1; also elsewhere on the board
I2C0_OFF: R9.2, U1.32 (IO39); also elsewhere on the board
I2C1_OFF: R10.2, U1.33 (IO40); also elsewhere on the board
OLED_RES_N: R6.1, U1.38 (IO2); also elsewhere on the board
OLED_SCL: U1.17 (IO9); also elsewhere on the board
OLED_SDA: U1.12 (IO8); also elsewhere on the board
PORT_OE_N: R7.2, U1.23 (IO21); also elsewhere on the board
SPARE0: TP3.1, U1.24 (IO47)
SPARE1: TP4.1, U1.25 (IO48)
UART_OE_N: R8.2, U1.31 (IO38); also elsewhere on the board
UART_RX_MCU: U1.11 (IO18); also elsewhere on the board
UART_TX_MCU: U1.10 (IO17); also elsewhere on the board
USB_DN: U1.13 (USB_D-); also elsewhere on the board
USB_DP: U1.14 (USB_D+); also elsewhere on the board
VBUS: TP6.1; also elsewhere on the board
VTREF_ADC: U1.39 (IO1); also elsewhere on the board

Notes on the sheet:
• Ref: docs/pin-allocation.md
• Reset defaults: target ports isolated, FPGA held in reset, aux outputs off.
ESP32-S3 CONTROL PLANE
• Straps GPIO3/45/46 unconnected; GPIO35-37 belong to the octal PSRAM.
• Native USB (GPIO19/20) = programming, serial/JTAG and PC link; no USB-UART chip.
• Both hardware I2C controllers serve the target as slaves; OLED uses software I2C.
